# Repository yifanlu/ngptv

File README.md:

ngptv
=====
This is an attempt at making an HDMI adapter for the Vita. It does not work 
because the ADV7533 does not support the auto clock stopping that the Vita uses 
to save battery on the MIPI DSI clock. There are two ways of getting it to 
work.

1. Replace the ADV7533 with another part that supports MIPI clock going from 
HS to LP mode when the data lanes are not in use. There are no other DSI to 
HDMI part, but you might get away with stacking a DSI to eDP and eDP to HDMI 
for example. Another way is to use a FPGA and convert the signals manually.
2. Creating some custom part to "filter" the stopped clock to a continuous 
clock. There does not appear to be any off-the-shelf part that does this and 
I've tried looking into re-purposing jitter correctors but they don't work 
because they average out the clock signals instead of locking on to the highest 
frequency.

Both are too much work for me to consider doing, so I will leave this non-
working project as is. Included are two designs. First is ngptv, which is 
supposed to be a small board that fits inside the Vita. Due to the design 
constraints of the ADV7533 (small pitch BGA) which requires > 6 layers and the 
small size requirement of all components, it does not seem feasible for me to 
prototype (too expensive and I don't have the right equipment to assemble).
Additionally, the ADV7533 is a NDA part that requires a HDMI license to buy.

The second design is ngptv lite which is designed to connect directly to a 
[B-LCDAD-HDMI](http://www.st.com/en/development-tools/b-lcdad-hdmi1.html) 
daughterboard. This $30 board contains a ADV7533 and was originally designed to 
work with a ST evaluation board. We instead connect it to the ngptv lite which 
has a microcontroller to interface with ADV7533 as well as a redriver for MIPI 
DSI. Using a 
[FFTP-07-D-03.85-01-N](https://www.samtec.com/products/fftp-07-d-03.85-01-n) 
cable, this connects to a breakout board placed inside the Vita that brings in 
the MIPI DSI signals from the exposed testpoints. The first version lacked the 
redriver, which seemed to still work (to the extent that it works if you 
manually set the Vita's MIPI clock to not use LP mode, which breaks the on 
screen video).

These designs are provided as-is under CC 4.0.

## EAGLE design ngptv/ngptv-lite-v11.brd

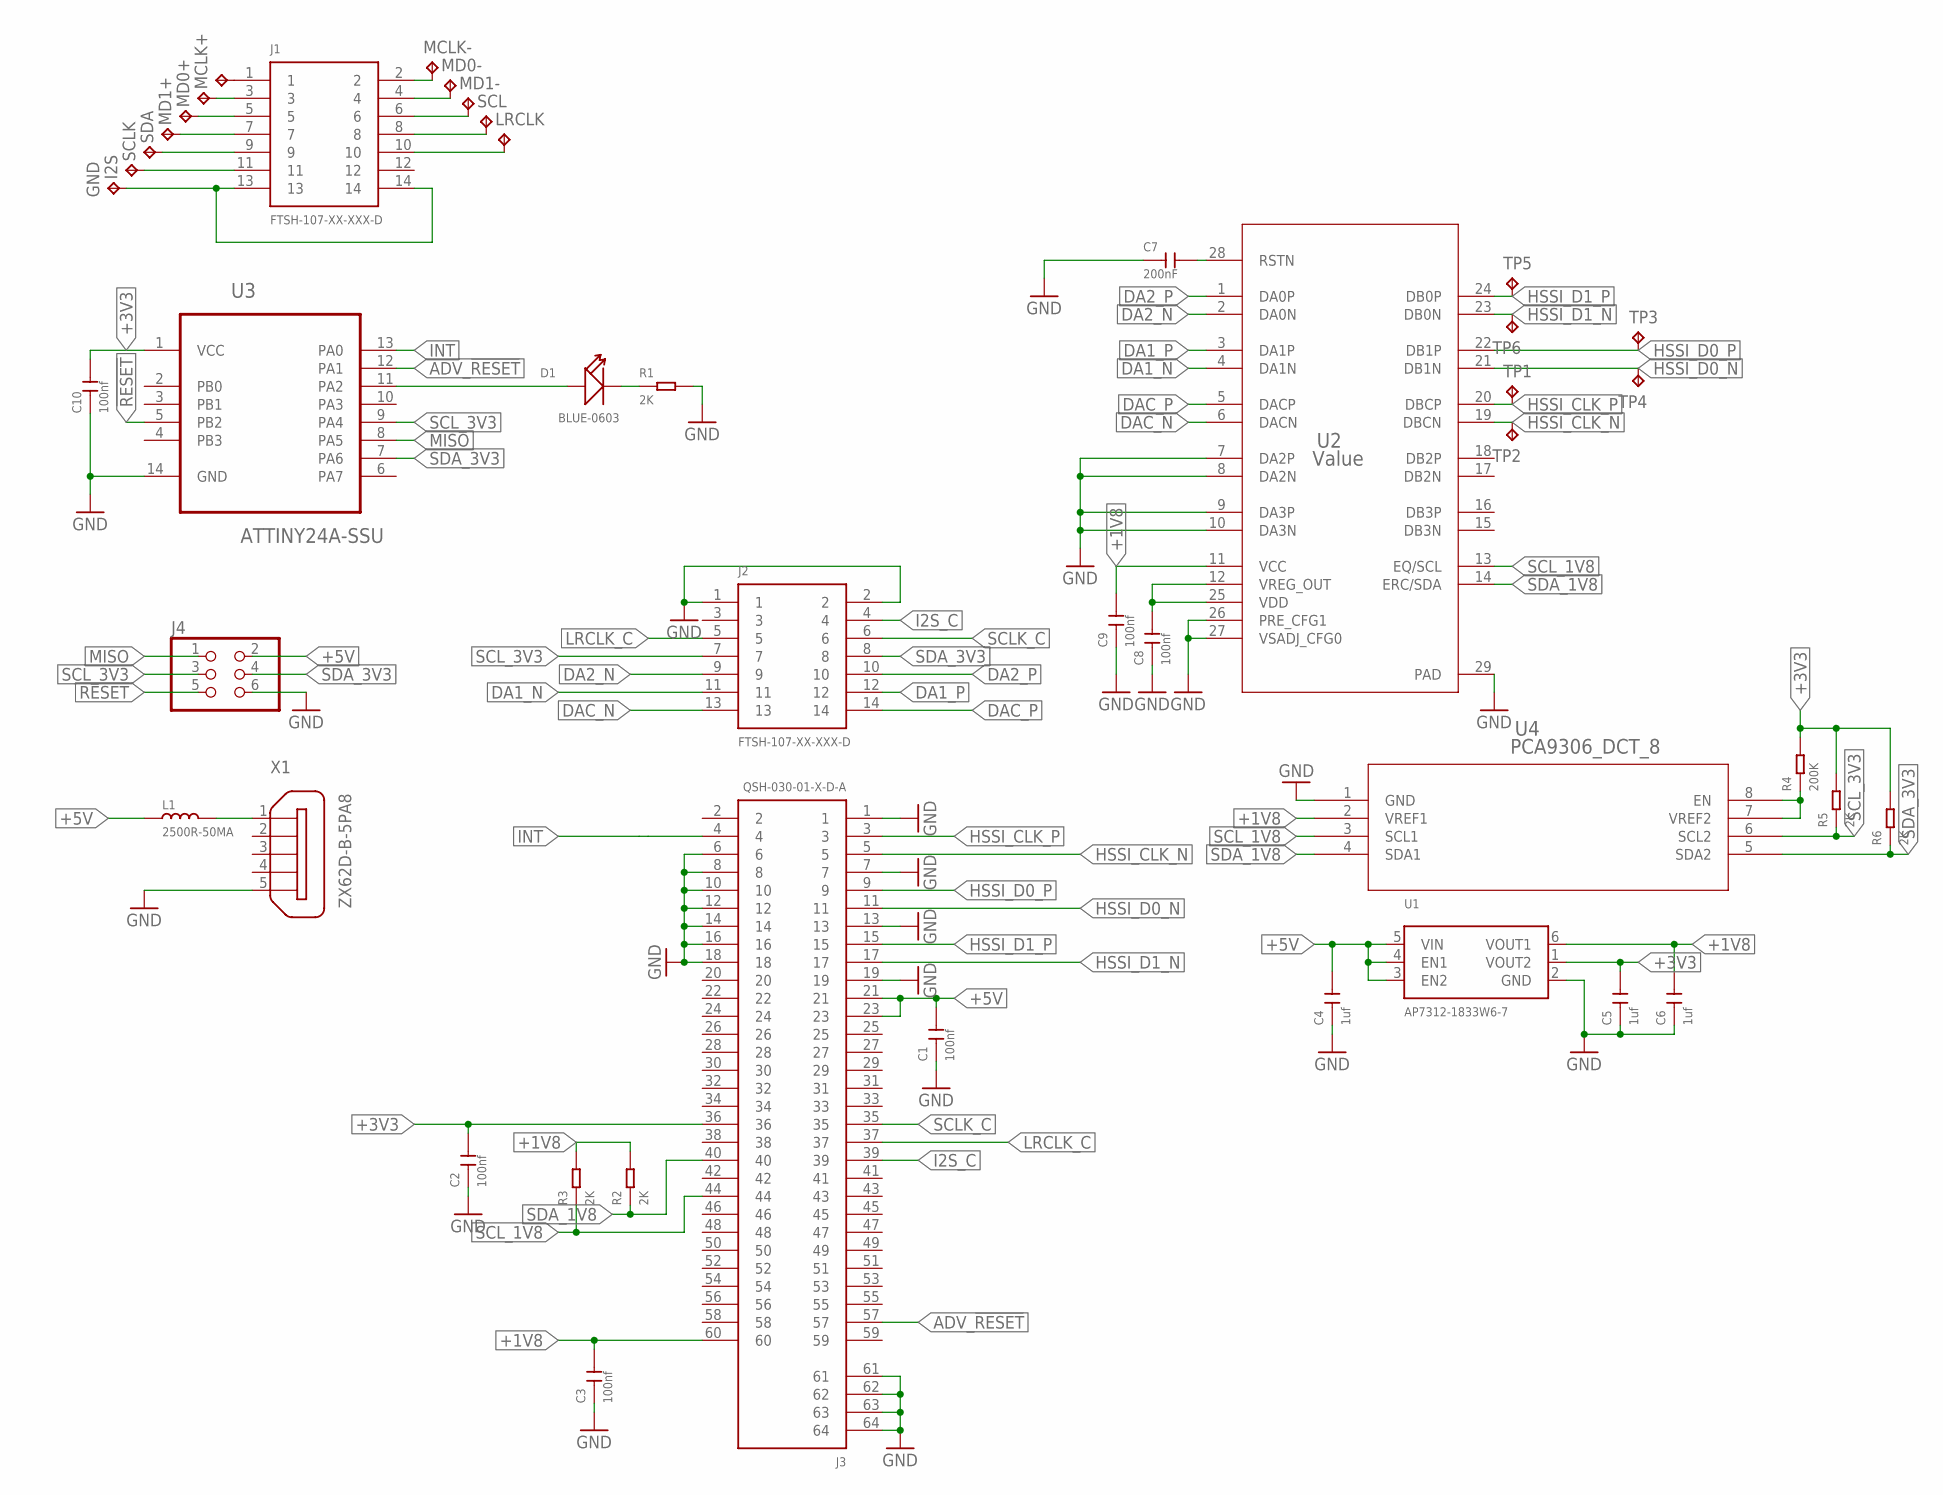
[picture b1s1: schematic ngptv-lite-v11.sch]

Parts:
C1, C2, C3, C8, C9, C10: 100nf; C0603
C4, C5, C6: 1uf; C0603
C7: 200nF; C0603
D1: BLUE-0603; LED-0603
GND: TPTP14R; TP14R
I2S: TPTP12R; TP12R
J1, J2: FTSH-107-XX-XXX-D
J3: QSH-030-01-X-D-A
J4: PINHD-2X3/90; 2X03/90
L1: 2500R-50MA; L0603
LRCLK: TPTP12R; TP12R
MCLK+: TPTP12R; TP12R
MCLK-: TPTP12R; TP12R
MD0+, MD0-, MD1+, MD1-: TPTP12R; TP12R
R1, R2, R3, R5, R6: 2K; R0603
R4: 200K; R0603
SCL: TPTP12R; TP12R
SCLK: TPTP12R; TP12R
SDA: TPTP12R; TP12R
TP1, TP2, TP3, TP4, TP5, TP6: TPTP06SQ; TP06SQ
U1: AP7312-1833W6-7; SOT95P280X145-6N
U2: Value; RHR0028A_NV
U3: ATTINY24A-SSU; SOIC127P600X175-14N
U4: PCA9306_DCT_8; DCT8
X1: ZX62D-B-5PA8

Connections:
!RESET: J4.5, U3.5 (PB2)
+1V8: C3.2, C6.2, C9.2, J3.60, R2.2, R3.2, U1.6 (VOUT1), U2.11 (VCC), U4.2 (VREF1)
+3V3: C2.2, C5.2, C10.2, J3.36, R4.2, R5.2, R6.2, U1.1 (VOUT2), U3.1 (VCC)
+5V: C1.2, C4.2, J3.21, J3.23, J4.2, L1.1, U1.3 (EN2), U1.4 (EN1), U1.5 (VIN)
ADV_!RESET: J3.57, U3.12 (PA1)
DA1_N: J2.11, U2.4 (DA1N)
DA1_P: J2.12, U2.3 (DA1P)
DA2_N: J2.9, U2.2 (DA0N)
DA2_P: J2.10, U2.1 (DA0P)
DAC_N: J2.13, U2.6 (DACN)
DAC_P: J2.14, U2.5 (DACP)
GND: C1.1, C2.1, C3.1, C4.1, C5.1, C6.1, C7.1, C8.1, C9.1, C10.1, J2.1, J2.2, J3.1, J3.6, J3.7, J3.8, J3.10, J3.12, J3.13, J3.14, J3.16, J3.18, J3.19, J3.61, J3.62, J3.63, J3.64, J4.6, R1.2, U1.2 (GND), U2.7 (DA2P), U2.8 (DA2N), U2.9 (DA3P), U2.10 (DA3N), U2.26 (PRE_CFG1), U2.27 (VSADJ_CFG0), U2.29 (PAD), U3.14 (GND), U4.1 (GND), X1.5
GND_H: GND.TP, J1.13, J1.14
HSSI_CLK_N: J3.5, TP2.TP, U2.19 (DBCN)
HSSI_CLK_P: J3.3, TP1.TP, U2.20 (DBCP)
HSSI_D0_N: J3.11, TP4.TP, U2.21 (DB1N)
HSSI_D0_P: J3.9, TP3.TP, U2.22 (DB1P)
HSSI_D1_N: J3.17, TP6.TP, U2.23 (DB0N)
HSSI_D1_P: J3.15, TP5.TP, U2.24 (DB0P)
I2S: I2S.TP, J1.11
I2S_C: J2.4, J3.39
INT: J3.4, U3.13 (PA0)
LRCLK: J1.10, LRCLK.TP
LRCLK_C: J2.5, J3.37
MCLK_N: J1.2, MCLK-.TP
MCLK_P: J1.1, MCLK+.TP
MD0_N: J1.4, MD0-.TP
MD0_P: J1.3, MD0+.TP
MD1_N: J1.6, MD1-.TP
MD1_P: J1.5, MD1+.TP
MISO: J4.1, U3.8 (PA5)
SCL: J1.8, SCL.TP
SCLK: J1.9, SCLK.TP
SCLK_C: J2.6, J3.35
SCL_1V8: J3.44, R3.1, U2.13 (EQ/SCL), U4.3 (SCL1)
SCL_3V3: J2.7, J4.3, R5.1, U3.9 (PA4), U4.6 (SCL2)
SDA: J1.7, SDA.TP
SDA_1V8: J3.40, R2.1, U2.14 (ERC/SDA), U4.4 (SDA1)
SDA_3V3: J2.8, J4.4, R6.1, U3.7 (PA6), U4.5 (SDA2)
STATUS: D1.+, U3.11 (PA2)
STATUS_N: D1.-, R1.1
TI_!RESET: C7.2, U2.28 (RSTN)
USB_VBUS: L1.2, X1.1
VREF2: R4.1, U4.7 (VREF2), U4.8 (EN)
VREG_OUT: C8.2, U2.12 (VREG_OUT), U2.25 (VDD)

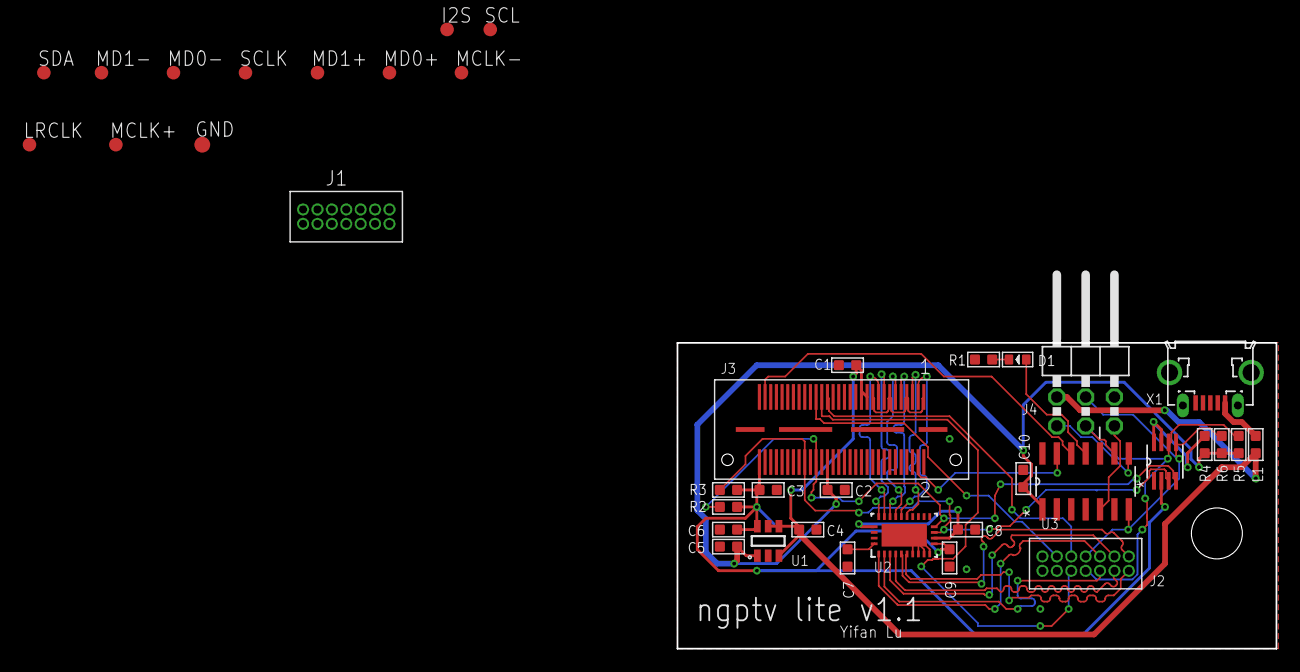
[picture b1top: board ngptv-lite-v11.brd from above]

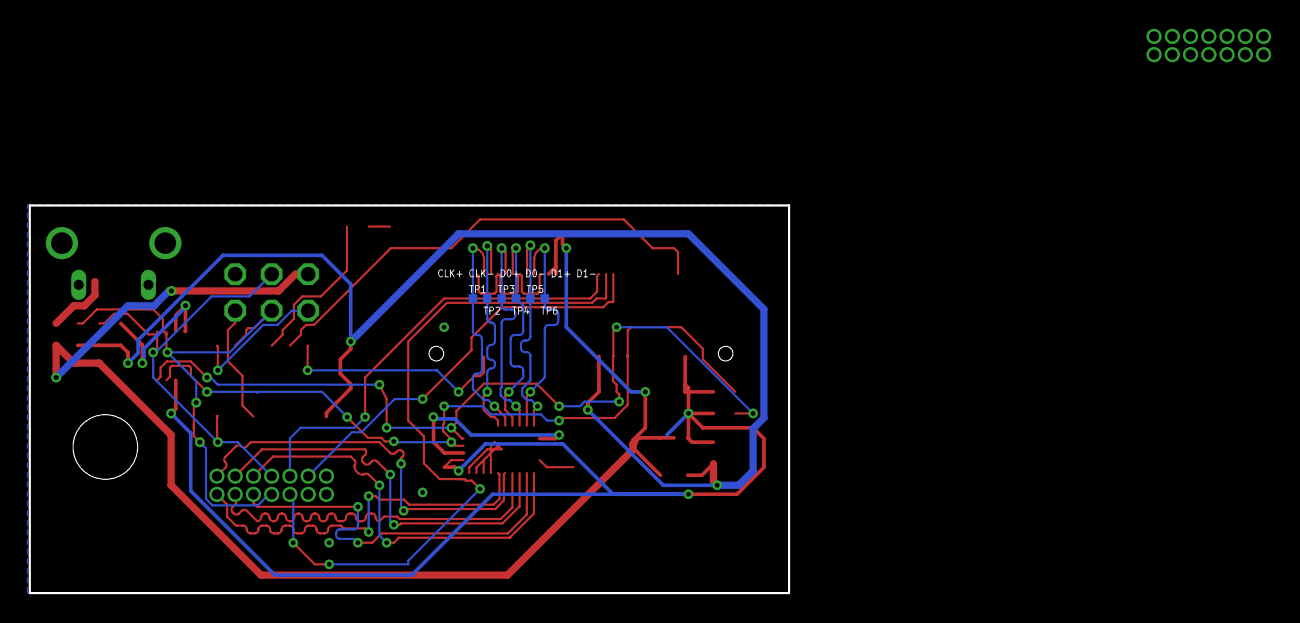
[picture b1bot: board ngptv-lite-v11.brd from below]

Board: 2 copper layers, 52.8 x 27.0 mm, 45 parts (6 on the bottom side), 45 nets.

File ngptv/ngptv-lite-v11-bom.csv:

Part,Value,Device,Package,Description,,
C1,100nf,CERAMIC-100NF-50V-10%-X7R(0603),C0603,302010138,,
C2,100nf,CERAMIC-100NF-50V-10%-X7R(0603),C0603,302010138,,
C3,100nf,CERAMIC-100NF-50V-10%-X7R(0603),C0603,302010138,,
C4,1uf,CERAMIC-1UF-25V-10%-X7R(0603),C0603,302010139,,
C5,1uf,CERAMIC-1UF-25V-10%-X7R(0603),C0603,302010139,,
C6,1uf,CERAMIC-1UF-25V-10%-X7R(0603),C0603,302010139,,
C7,200nF,CERAMIC-220NF-25V-10%-X7R(0603),C0603,302010073,,
C8,100nf,CERAMIC-100NF-50V-10%-X7R(0603),C0603,302010138,,
C9,100nf,CERAMIC-100NF-50V-10%-X7R(0603),C0603,302010138,,
C10,100nf,CERAMIC-100NF-50V-10%-X7R(0603),C0603,302010138,,
D1,BLUE-0603,SMD-LED-CLEAR-BLUE(0603),LED-0603,304090045,,
J1,FTSH-107-XX-XXX-D,FTSH-107-XX-XXX-D,FTSH-107-XX-XXX-D,"0.050X0.050"" CL THROUGH HOLE TERMINAL STRIP ASSEMBLY,14PINS.""",,
J2,FTSH-107-XX-XXX-D,FTSH-107-XX-XXX-D,FTSH-107-XX-XXX-D,"0.050X0.050"" CL THROUGH HOLE TERMINAL STRIP ASSEMBLY,14PINS.""",,
J3,QSH-030-01-X-D-A,QSH-030-01-X-D-A,QSH-030-01-X-D-A,"HIGH SPEED SOCKET STRIP, .5mm PITCH, 60 PINS.",,
J4,,PINHD-2X3/90,2X03/90,PIN HEADER,,
L1,2500R-50MA,SMD-FERRITE-BEAD-2500R-50MA(0603),L0603,303030020,,
R1,2K,SMD-RES-2K-5%-1/10W(0603),R0603,301010298,,
R2,2K,SMD-RES-2K-5%-1/10W(0603),R0603,301010113,,
R3,2K,SMD-RES-2K-5%-1/10W(0603),R0603,301010113,,
R4,200K,SMD-RES-200K-5%-1/10W(0603),R0603,301010212,,
R5,2K,SMD-RES-2K-5%-1/10W(0603),R0603,301010113,,
R6,2K,SMD-RES-2K-5%-1/10W(0603),R0603,301010113,,
U1,AP7312-1833W6-7,AP7312,SOT95P280X145-6N,,,
U2,SN75DPHY440SS,SN75DPHY440SS,RHR0028A_NV,,,
U3,ATTINY24A-SSU,ATTINY24A-SSU,SOIC127P600X175-14N,8-bit Microcontroller with In-System Programmable Flash,,
U4,PCA9306_DCT_8,PCA9306_DCT_8,DCT8,,,
X1,ZX62D-B-5PA8,ZX62D-B-5PA8,ZX62D-B-5PA8,"Micro USB Type B Connector - Standard, Shell Through Hole",,

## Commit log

2017-09-18 Finished schematic
2017-09-27 Updated sch
2017-09-27 Changed part
2017-09-27 Added lite version
2017-12-07 ngptv lite v1.1 design
2017-12-07 Minor modifications for fab
2017-12-30 Added BOM
2017-12-30 Added python init code
2017-12-30 Added readme
